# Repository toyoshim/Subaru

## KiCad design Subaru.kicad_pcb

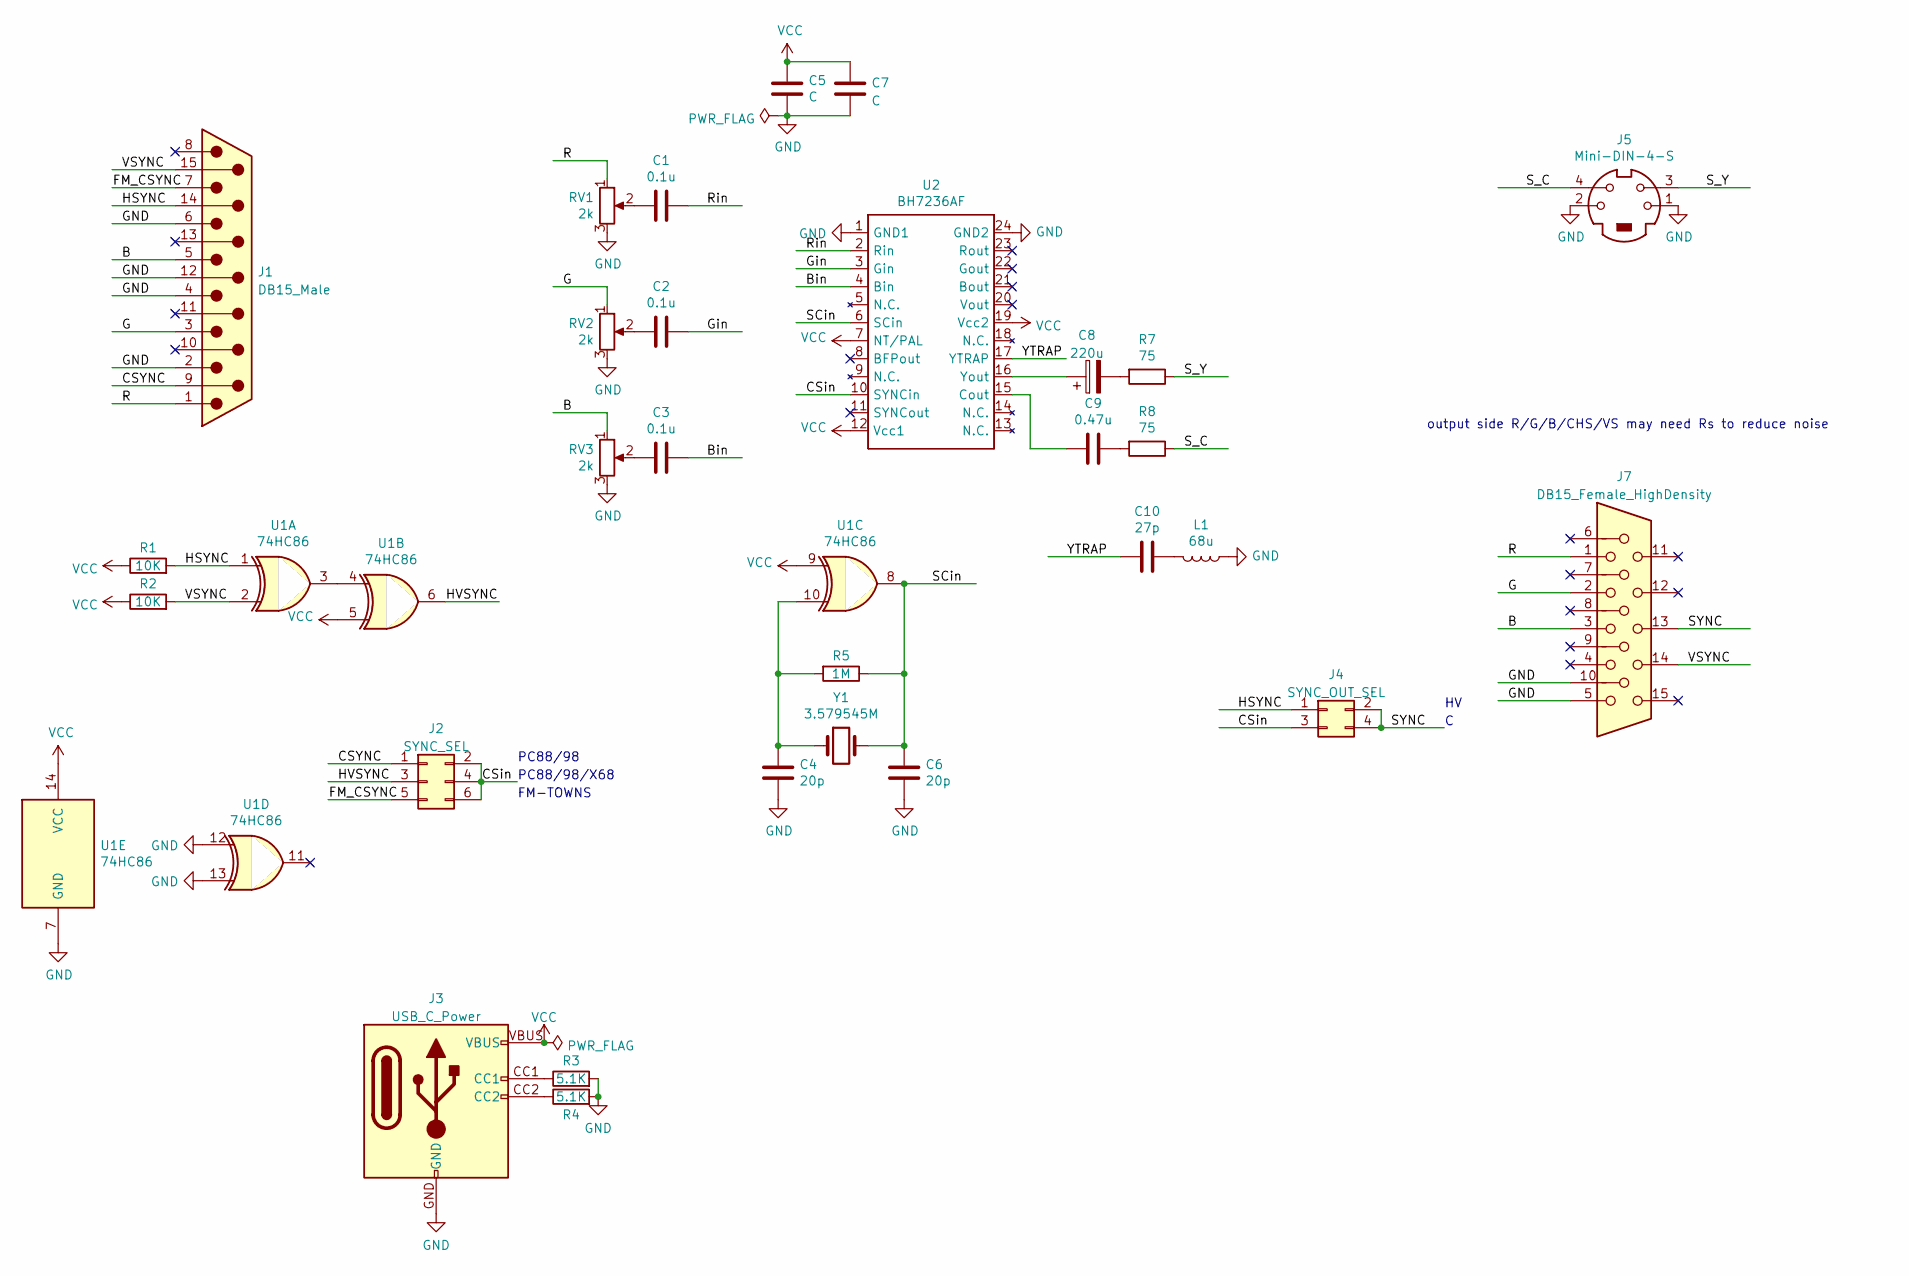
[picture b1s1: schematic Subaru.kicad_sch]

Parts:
C1, C2, C3: 0.1u; C_0603_1608Metric
C4, C6: 20p; C_0603_1608Metric
C5, C7: C; C_0603_1608Metric
C8: 220u; CP_Radial_D5.0mm_P2.50mm
C9: 0.47u; C_0603_1608Metric
C10: 27p; C_0603_1608Metric
J1: DB15_Male; DSUB-15_Male_Horizontal_P2.77x2.84mm_EdgePinOffset7.70mm_Ho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
J2: SYNC_SEL; PinHeader_2x03_P2.54mm_Vertical
J3: USB_C_Power; USB4125-GF-A
J4: SYNC_OUT_SEL; PinHeader_2x02_P2.54mm_Vertical
J5: Mini-DIN-4-S; MINI-DIN-4-DI-6798-4
J7: DB15_Female_HighDensity; DSUB-15-HD_Female_A_HDF15A_KG_TAXB
L1: 68u; L_0805_2012Metric
R1, R2: 10K; R_0603_1608Metric
R3, R4: 5.1K; R_0603_1608Metric
R5: 1M; R_0603_1608Metric
R7, R8: 75; R_0603_1608Metric
RV1, RV2, RV3: 2k; RV-RM-065
U1: 74HC86; SOIC-14_3.9x8.7mm_P1.27mm
U2: BH7236AF; SOIC-24_4.4x15.4mm_P1.27mm
Y1: 3.579545M; Crystal_HC49-4H_Vertical

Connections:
/B: J1.5, J7.3, RV3.1
/Bin: C3.1, U2.4 (Bin)
/CSYNC: J1.9, J2.1
/CSin: J2.2, J2.4, J2.6, J4.3, U2.10 (SYNCin)
/FM_CSYNC: J1.7, J2.5
/G: J1.3, J7.2, RV2.1
/Gin: C2.1, U2.3 (Gin)
/HSYNC: J1.14, J4.1, R1.2, U1.1
/HVSYNC: J2.3, U1.6
/R: J1.1, J7.1, RV1.1
/Rin: C1.1, U2.2 (Rin)
/SCin: C6.1, R5.1, U1.8, U2.6 (SCin), Y1.2
/SYNC: J4.2, J4.4, J7.13
/S_C: J5.4, R8.1
/S_Y: J5.3, R7.1
/VSYNC: J1.15, J7.14, R2.2, U1.2
/YTRAP: C10.2, U2.17 (YTRAP)
GND: C4.2, C5.2, C6.2, C7.2, J1.2, J1.4, J1.6, J1.12, J3.GND, J5.1, J5.2, J7.5, J7.10, L1.1, R3.2, R4.2, RV1.3, RV2.3, RV3.3, U1.7 (GND), U1.12, U1.13, U2.1 (GND1), U2.24 (GND2)
unnamed: C1.2, RV1.2
unnamed: C2.2, RV2.2
unnamed: C3.2, RV3.2
unnamed: C4.1, R5.2, U1.10, Y1.1
unnamed: C8.1, U2.16 (Yout)
unnamed: C8.2, R7.2
unnamed: C9.1, R8.2
unnamed: C9.2, U2.15 (Cout)
unnamed: C10.1, L1.2
unnamed: J3.CC1, R3.1
unnamed: J3.CC2, R4.1
unnamed: U1.3, U1.4
VCC: C5.1, C7.1, J3.VBUS, R1.1, R2.1, U1.5, U1.9, U1.14 (VCC), U2.7 (NT/PAL), U2.12 (Vcc1), U2.19 (Vcc2)

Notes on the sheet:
FM-TOWNS
PC88/98
PC88/98/X68
output side R/G/B/CHS/VS may need Rs to reduce noise

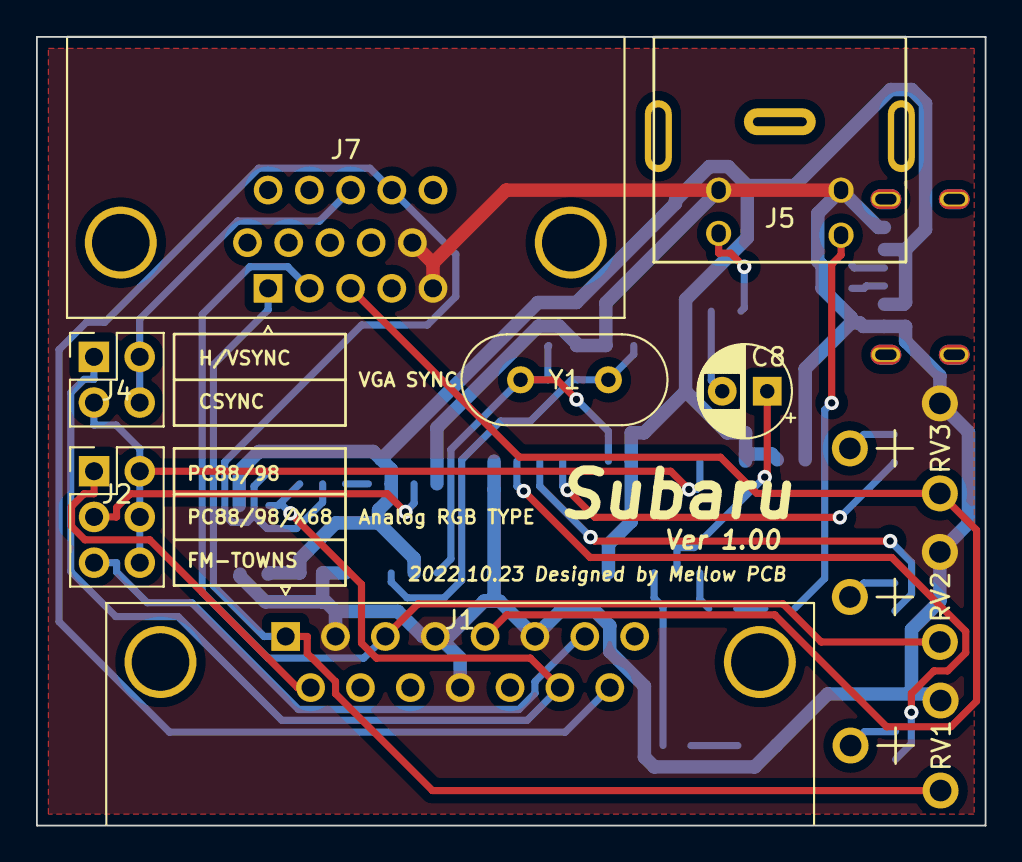
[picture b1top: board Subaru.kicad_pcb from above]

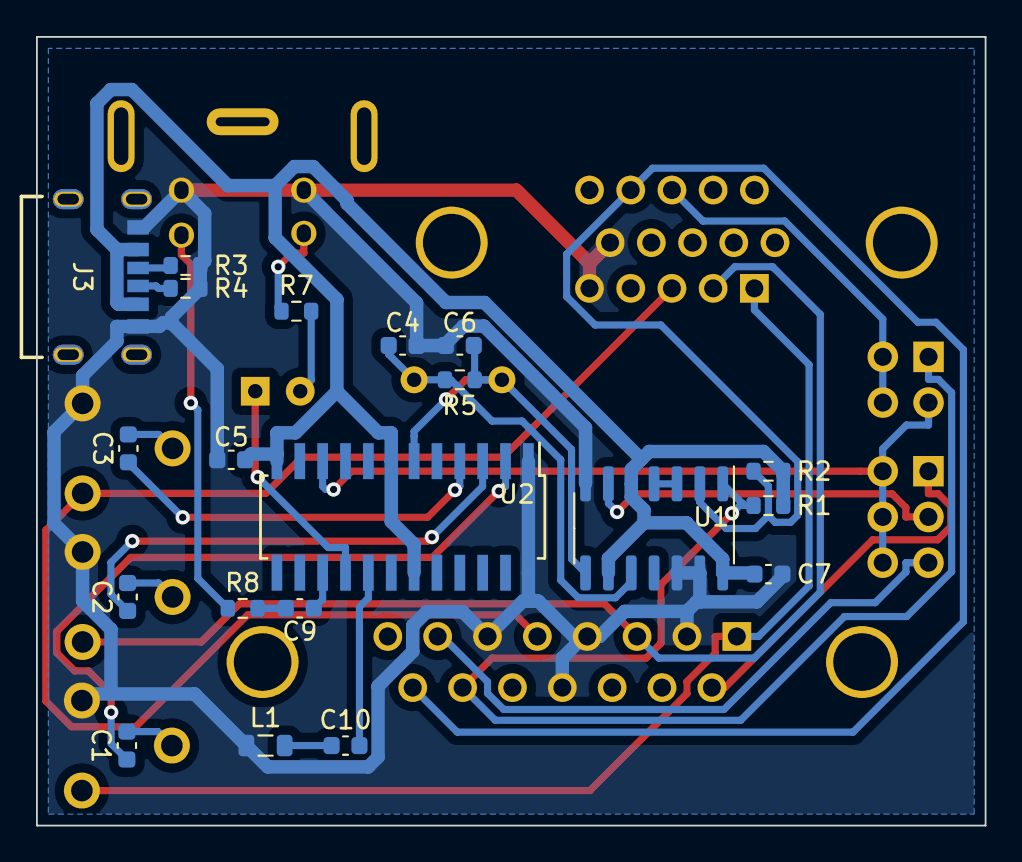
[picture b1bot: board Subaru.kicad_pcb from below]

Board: 2 copper layers, 52.7 x 43.8 mm, 30 parts (20 on the bottom side), 31 nets.

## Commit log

2022-11-07 update sch to have capacitor's value
2022-11-07 feedback from the 1st lot
    - modify footprint for S connector
    - add a comment on noise in the circuit
